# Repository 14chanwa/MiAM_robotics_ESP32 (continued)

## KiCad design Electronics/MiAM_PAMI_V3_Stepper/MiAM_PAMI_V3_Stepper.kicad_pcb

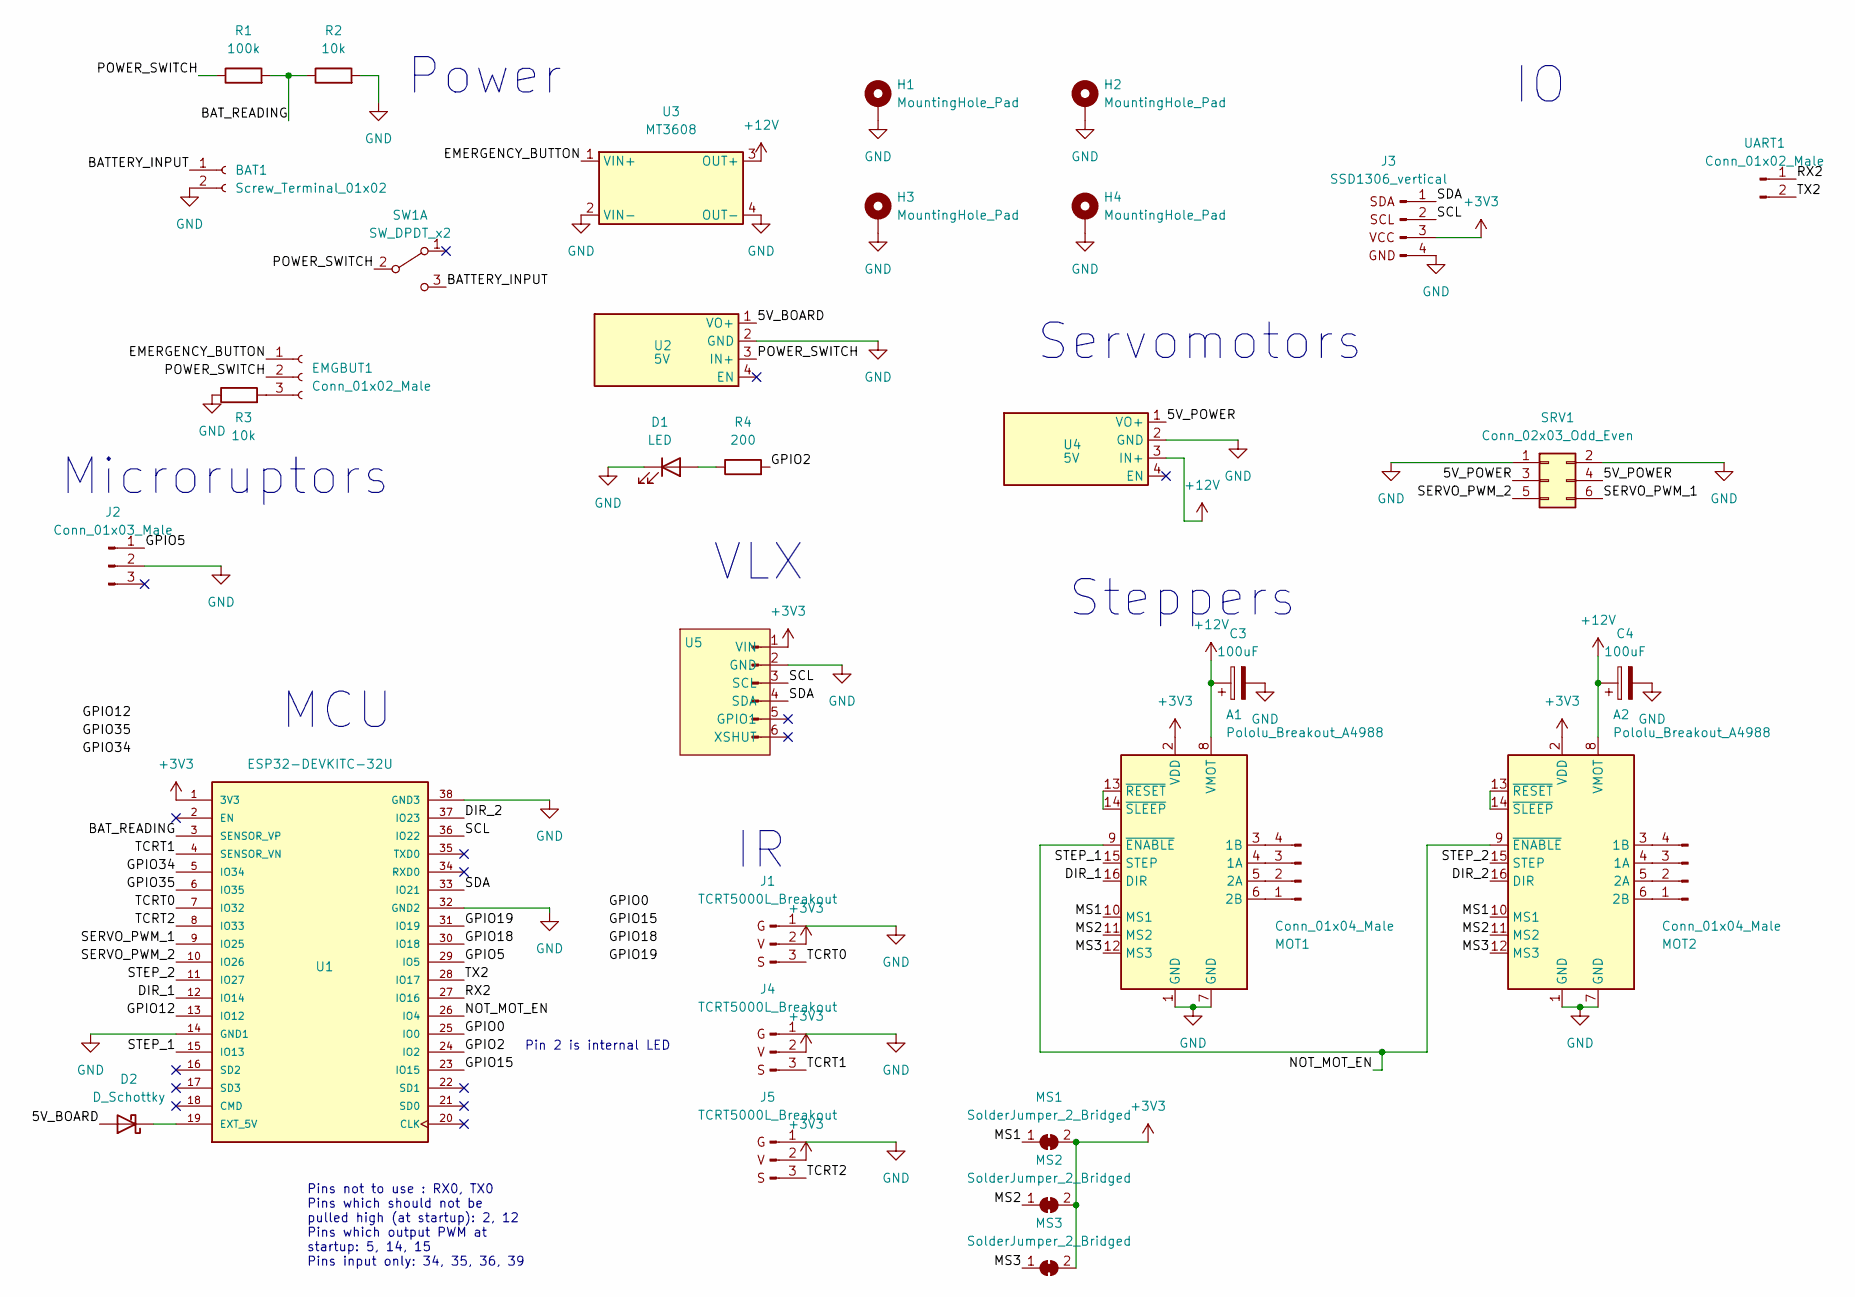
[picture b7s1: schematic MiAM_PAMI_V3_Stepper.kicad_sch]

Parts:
A1, A2: Pololu_Breakout_A4988; Pololu_Breakout-16_15.2x20.3mm
BAT1: Screw_Terminal_01x02; JST_PH_B2B-PH-K_1x02_P2.00mm_Vertical
C3, C4: 100uF; CP_Radial_D6.3mm_P2.50mm
D1: LED; LED_D3.0mm
D2: D_Schottky; D_SOD-323_HandSoldering
EMGBUT1: Conn_01x02_Male; JST_PH_B3B-PH-K_1x03_P2.00mm_Vertical
H1, H2, H3, H4: MountingHole_Pad; MountingHole_3.2mm_M3_DIN965_Pad
J1, J4, J5: TCRT5000L_Breakout
J2: Conn_01x03_Male; Microruptor
J3: SSD1306_vertical
MOT1, MOT2: Conn_01x04_Male; JST_SH_BM04B-SRSS-TB_1x04-1MP_P1.00mm_Vertical
MS1, MS2, MS3: SolderJumper_2_Bridged; SolderJumper-2_P1.3mm_Bridged_RoundedPad1.0x1.5mm
R1: 100k; R_0805_2012Metric_Pad1.20x1.40mm_HandSolder
R2, R3: 10k; R_0805_2012Metric_Pad1.20x1.40mm_HandSolder
R4: 200; R_0805_2012Metric
SRV1: Conn_02x03_Odd_Even; PinHeader_2x03_P2.54mm_Vertical
SW1: SW_DPDT_x2; SS-12D11
U1: ESP32-DEVKITC-32U; ESP32U-ShieldPattern
U2, U4: 5V; VoltageRegulator
U3: MT3608
U5: PinHeader_1x06_P2.54mm_Vertical
UART1: Conn_01x02_Male; PinHeader_1x02_P2.54mm_Vertical

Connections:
+3V3: A1.2 (VDD), A2.2 (VDD), J1.2 (V), J3.3 (VCC), J4.2 (V), J5.2 (V), MS1.2 (B), MS2.2 (B), MS3.2 (B), U1.1 (3V3), U5.1 (VIN)
+12V: A1.8 (VMOT), A2.8 (VMOT), C3.1, C4.1, U3.3 (OUT+), U4.3 (IN+)
/5V_BOARD: D2.2 (A), U2.1 (VO+)
/5V_POWER: SRV1.3, SRV1.4, U4.1 (VO+)
/BATTERY_INPUT: BAT1.1, SW1.3 (C)
/BAT_READING: R1.2, R2.1, U1.3 (SENSOR_VP)
/DIR_1: A1.16 (DIR), U1.12 (IO14)
/DIR_2: A2.16 (DIR), U1.37 (IO23)
/EMERGENCY_BUTTON: EMGBUT1.1, U3.1 (VIN+)
/GPIO0: U1.25 (IO0); also elsewhere on the board
/GPIO2: R4.2, U1.24 (IO2)
/GPIO5: J2.1, U1.29 (IO5)
/GPIO12: U1.13 (IO12); also elsewhere on the board
/GPIO15: U1.23 (IO15); also elsewhere on the board
/GPIO18: U1.30 (IO18); also elsewhere on the board
/GPIO19: U1.31 (IO19); also elsewhere on the board
/GPIO34: U1.5 (IO34); also elsewhere on the board
/GPIO35: U1.6 (IO35); also elsewhere on the board
/MS1: A1.10 (MS1), A2.10 (MS1), MS1.1 (A)
/MS2: A1.11 (MS2), A2.11 (MS2), MS2.1 (A)
/MS3: A1.12 (MS3), A2.12 (MS3), MS3.1 (A)
/NOT_MOT_EN: A1.9 (~ENABLE), A2.9 (~ENABLE), U1.26 (IO4)
/POWER_SWITCH: EMGBUT1.2, R1.1, SW1.2 (B), U2.3 (IN+)
/RX2: U1.27 (IO16), UART1.1
/SCL: J3.2 (SCL), U1.36 (IO22), U5.3 (SCL)
/SDA: J3.1 (SDA), U1.33 (IO21), U5.4 (SDA)
/SERVO_PWM_1: SRV1.6, U1.9 (IO25)
/SERVO_PWM_2: SRV1.5, U1.10 (IO26)
/STEP_1: A1.15 (STEP), U1.15 (IO13)
/STEP_2: A2.15 (STEP), U1.11 (IO27)
/TCRT0: J1.3 (S), U1.7 (IO32)
/TCRT1: J4.3 (S), U1.4 (SENSOR_VN)
/TCRT2: J5.3 (S), U1.8 (IO33)
/TX2: U1.28 (IO17), UART1.2
GND: A1.1 (GND), A1.7 (GND), A2.1 (GND), A2.7 (GND), BAT1.2, C3.2, C4.2, D1.1 (K), H1.1, H2.1, H3.1, H4.1, J1.1 (G), J2.2, J3.4 (GND), J4.1 (G), J5.1 (G), R2.2, R3.1, SRV1.1, SRV1.2, U1.14 (GND1), U1.32 (GND2), U1.38 (GND3), U2.2 (GND), U3.2 (VIN-), U3.4 (OUT-), U4.2 (GND), U5.2 (GND)
unnamed: A1.4 (1A), MOT1.3
unnamed: A1.3 (1B), MOT1.4
unnamed: A1.5 (2A), MOT1.2
unnamed: A1.6 (2B), MOT1.1
unnamed: A1.13 (~RESET), A1.14 (~SLEEP)
unnamed: A2.4 (1A), MOT2.3
unnamed: A2.3 (1B), MOT2.4
unnamed: A2.5 (2A), MOT2.2
unnamed: A2.6 (2B), MOT2.1
unnamed: A2.13 (~RESET), A2.14 (~SLEEP)
unnamed: D1.2 (A), R4.1
unnamed: D2.1 (K), U1.19 (EXT_5V)
unnamed: EMGBUT1.3, R3.2

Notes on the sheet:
Pins not to use : RX0, TX0 Pins which should not be pulled high (at startup): 2, 12 Pins which output PWM at startup: 5, 14, 15 Pins input only: 34, 35, 36, 39
Power
MCU
Microruptors
Pin 2 is internal LED
VLX
Steppers
Servomotors

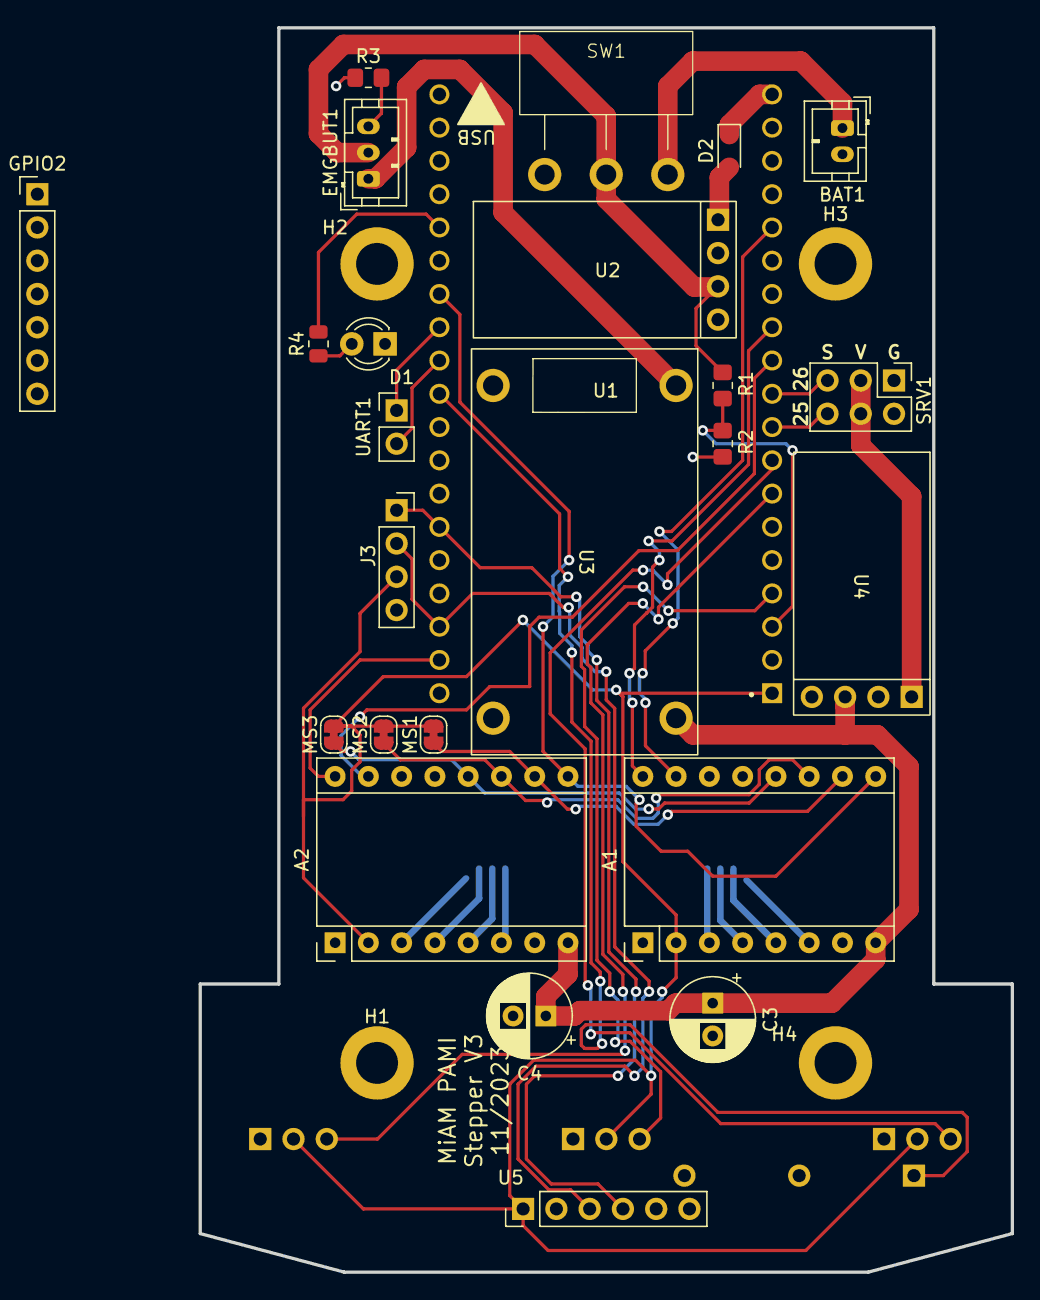
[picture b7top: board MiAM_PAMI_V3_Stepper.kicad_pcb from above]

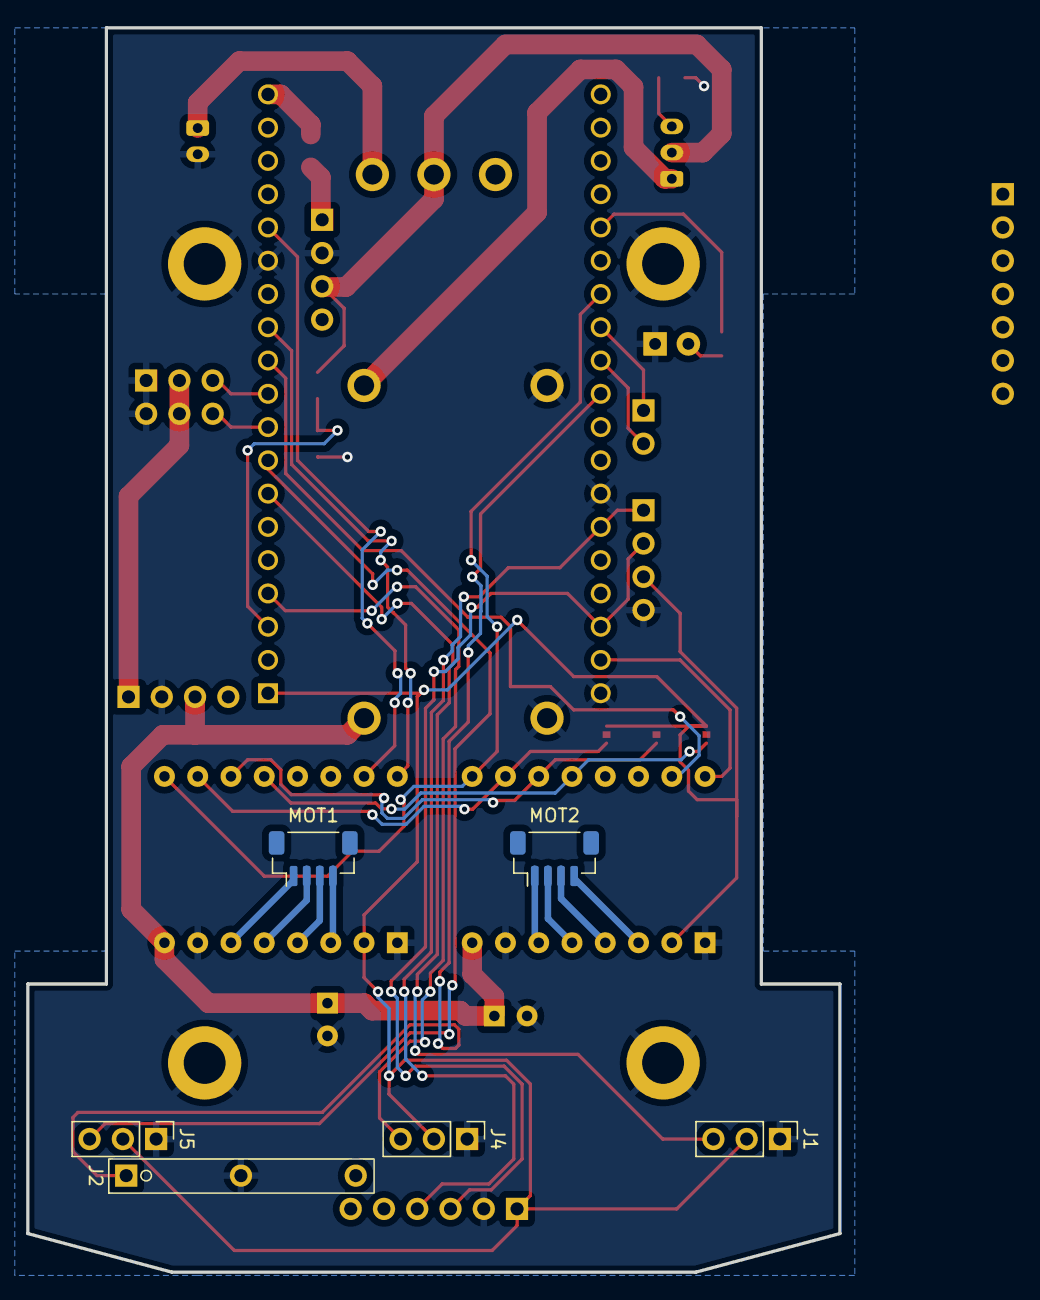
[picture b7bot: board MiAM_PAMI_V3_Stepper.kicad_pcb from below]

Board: 2 copper layers, 62.0 x 95.0 mm, 35 parts (6 on the bottom side), 48 nets.

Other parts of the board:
GPIO2: Conn_01x07_Male; PinHeader_1x07_P2.54mm_Vertical

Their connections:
/GPIO0: GPIO2.1; also elsewhere on the board
/GPIO12: GPIO2.2; also elsewhere on the board
/GPIO15: GPIO2.3; also elsewhere on the board
/GPIO18: GPIO2.4; also elsewhere on the board
/GPIO19: GPIO2.5; also elsewhere on the board
/GPIO34: GPIO2.6; also elsewhere on the board
/GPIO35: GPIO2.7; also elsewhere on the board

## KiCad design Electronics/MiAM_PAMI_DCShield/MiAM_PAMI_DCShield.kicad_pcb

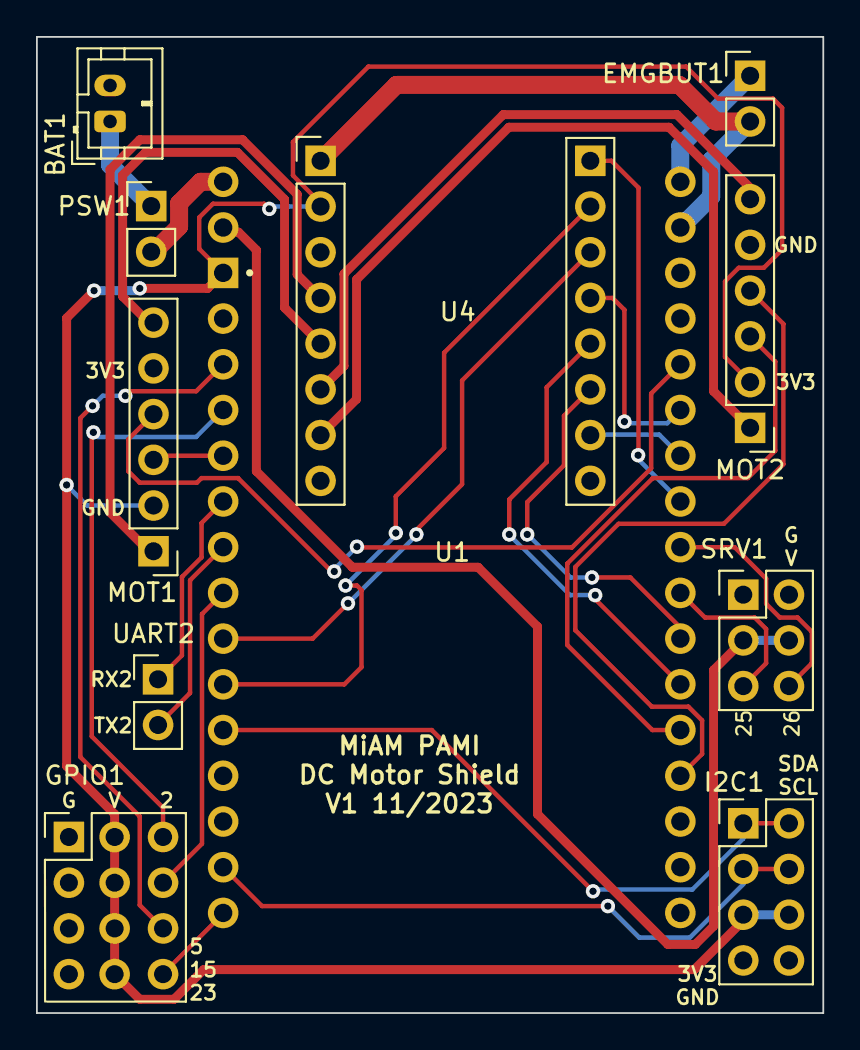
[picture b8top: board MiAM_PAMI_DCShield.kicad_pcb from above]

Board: 2 copper layers, 43.7 x 54.2 mm, 11 parts (0 on the bottom side), 32 nets.

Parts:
BAT1: Screw_Terminal_01x02; JST_PH_B2B-PH-K_1x02_P2.00mm_Vertical
EMGBUT1: Conn_01x02_Male; PinHeader_1x02_P2.54mm_Vertical
GPIO1: PinHeader_3x4_P2.54mm_Vertical
I2C1: Conn_02x04_Odd_Even; PinHeader_2x04_P2.54mm_Vertical
MOT1, MOT2: Conn_01x06_Male; PinHeader_1x06_P2.54mm_Vertical
PSW1: Conn_01x02_Male; PinHeader_1x02_P2.54mm_Vertical
SRV1: Conn_02x03_Odd_Even; PinHeader_2x03_P2.54mm_Vertical
U1: ESP32-DEVKIT-V1; ESP32_ShieldPattern
U4: TB6612FNG
UART2: Conn_01x02_Male; PinHeader_1x02_P2.54mm_Vertical

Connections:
+3V3: GPIO1.5, GPIO1.6, GPIO1.7, GPIO1.8, I2C1.5, I2C1.6, MOT1.2, MOT2.2, U1.1 (3V3), U4.2 (VCC)
+12V: EMGBUT1.1, U1.SH2 (12V)
/1A: U1.9 (D18), U4.14 (AIN1)
/1Y: MOT1.1, U4.4 (AO1)
/2A: U1.10 (D19), U4.15 (AIN2)
/2Y: MOT1.6, U4.5 (AO2)
/3A: U1.21 (D32), U4.12 (BIN1)
/3Y: MOT2.1, U4.7 (BO1)
/4A: U1.22 (D33), U4.11 (BIN2)
/4Y: MOT2.6, U4.6 (BO2)
/5V_POWER: SRV1.3, SRV1.4, U1.SH3 (SERVO_V)
/BATTERY_INPUT: BAT1.1, PSW1.1
/EMERGENCY_BUTTON: EMGBUT1.2, U1.SH1 (EMG_BUT), U4.1 (VM)
/EN12: U1.25 (D27), U4.16 (PWMA)
/EN34: U1.26 (D14), U4.10 (PWMB)
/ENCODER_A1: MOT1.4, U1.28 (D13)
/ENCODER_A2: MOT2.4, U1.19 (D34)
/ENCODER_B1: MOT1.3, U1.5 (D4)
/ENCODER_B2: MOT2.3, U1.20 (D35)
/GPIO2: GPIO1.9, U1.4 (D2)
/GPIO5: GPIO1.10, U1.8 (D5)
/GPIO15: GPIO1.11, U1.3 (D15)
/GPIO23: GPIO1.12, U1.15 (D23)
/POWER_SWITCH: PSW1.2, U1.SH4 (POW_SW)
/RX2: U1.6 (RX2), UART2.1
/SCL: I2C1.3, I2C1.4, U1.14 (D22)
/SDA: I2C1.1, I2C1.2, U1.11 (D21)
/SERVO_PWM_1: SRV1.5, U1.23 (D25)
/SERVO_PWM_2: SRV1.6, U1.24 (D26)
/STBY: U1.27 (D12), U4.13 (STBY)
/TX2: U1.7 (TX2), UART2.2
GND: BAT1.2, GPIO1.1, GPIO1.2, GPIO1.3, GPIO1.4, I2C1.7, I2C1.8, MOT1.5, MOT2.5, SRV1.1, SRV1.2, U1.2 (GND), U1.18 (VN), U1.29 (GND), U4.3 (PGND), U4.8 (PGND), U4.9 (PGND)

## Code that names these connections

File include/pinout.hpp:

#ifndef _PINOUT_HEADER
#define _PINOUT_HEADER

/////////////////////////////////////////////
// Pins
/////////////////////////////////////////////

// #define LED_BUILTIN 2

#define IN1_A 25
#define IN2_A 26
#define IN1_B 32
#define IN2_B 33
#define EN_A 27
#define EN_B 14

#define ENCODER_A1 2
#define ENCODER_B1 4

#define ENCODER_A2 34
#define ENCODER_B2 35

#define BAT_READING 36

/////////////////////////////////////////////
// Resistor values
/////////////////////////////////////////////

#define R1 20000.0
#define R2 4700.0

/////////////////////////////////////////////
// Motor & encoder specs
/////////////////////////////////////////////

#define MOTOR_REDUCTION_FACTOR 100.0
#define MOTOR_RATED_RPM 220.0
#define ENCODER_PULSE_PER_REVOLUTION 28
#define LEFT_ENCODER_ID 0
#define RIGHT_ENCODER_ID 1

#endif

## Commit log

2023-07-31 Start implementing PID
2023-07-31 Write a specific Motor class
2023-07-31 Change unit to rad/s
2023-08-01 Change control unit to PWM
2023-08-05 Put code in a separate folder
2023-08-05 Add first version of pcb
2023-08-06 Add miam utils and kinematics
2023-08-08 Do straight lines & fix params
2023-08-08 Add motioncontroller
2023-08-08 Change calibration trajectory
2023-08-09 Ajoute logger UDP Teleplot
2023-08-09 Use float instead of double to optimize speed
2023-08-09 Add LED heartbeat
2023-08-09 Set compiler optimization
2023-08-09 Fixups
2023-08-09 Add credentials handling
2023-09-02 Update driver and add ota update
2023-10-16 Tweak parameters for new design
2023-10-16 Add first PAMI CAD
2023-10-18 Make more condensed version of pcb
2023-10-23 Make genric robot wheel structure
2023-10-28 Add modular structure for stepper & dc pami
2023-10-28 Fix initial PAMI pcb
2023-10-28 Add 3 PCB for DC & Stepper PAMI
2023-10-28 Fix MT3608 footprint
2023-10-28 Fix shield footprint
2023-11-01 Faster DC
2023-11-03 Add V2 of PAMI stepper
2023-11-03 Fix pcb & add driver board
2023-11-06 Put stepper driver on main board
2023-11-06 Begin optimizing stepper code
2023-11-06 Fix new stepper code
2023-11-06 Switch to ArduinoOTA and cleanup
2023-11-24 Switch to esp-idf+arduino & fix lag issues
2023-11-26 Initial commit PAMI V3
2023-11-26 Init pami v3
2023-11-26 Fix PCB for v3
2023-11-26 Fix pcb v3
2023-11-26 Fixes, adds vlx & tcrt
2023-11-29 PCB order 2023-11-29
2024-01-21 Functional stepper code for a square
2024-01-21 Add ssd1306 and semaphores
2024-02-06 Add DC PAMI board
2024-02-17 Robot now waits for broadcasted traj
2024-02-17 Fix message length bug
2024-02-17 Enhance ssd1306 message
2024-02-18 Add slowdown with vlx
2024-02-18 Fix PCB
2024-02-18 Add message type handling
2024-02-18 Receive IDs
2024-02-18 Fix DC PAMI schematic
2024-02-18 Display ID on screen
2024-02-19 Add match time handling
2024-03-09 Working DC PAMI (need invert one motor)
2024-03-09 Fix invert motor
2024-03-13 Add servo example code
2024-03-13 Clean servo code
2024-03-16 Update code with strategy
2024-03-16 Rework i2c tasks
2024-03-17 Make PAMI listen to UDP broadcasts
2024-03-17 Functional trajectories
2024-03-17 Update positions
2024-03-18 Init git for SupervisorBoard
2024-03-22 Make ethernet listening
2024-03-22 Add SupervisorBoard tft screen & routing
2024-03-25 Complete supervisor PCB
2024-03-25 Add front switches code
2024-03-29 Rework code structure
2024-03-30 Add telemetry handler & bf blinking
2024-03-30 Add Message parsing
2024-03-30 Fix TCP issue (not closing connections)
2024-03-30 Add PAMI message
2024-03-31 Fix issue with newer C++ versions
2024-03-31 Finish MatchState machine for robot loop & multiple BFs
2024-03-31 BF telemetry DC
2024-04-05 Block steppers in match ended state, handle switches, send reports to scd
2024-04-05 Add miam utils to SupervisorBoard, start interface
2024-04-05 Put report broadast in message handling
2024-04-06 Fix message sending & receiving for PAMI
2024-04-06 Add missing lib
2024-04-06 Add match
2024-04-06 Use wifi for SCD
2024-04-07 Return message
2024-04-07 Fix segfault in message sender
2024-04-07 BF comms: pami requests respnse
2024-04-28 Use float arrays as buffers for message
2024-04-28 Add tirette functionnality
2024-05-04 Add comm delay and battery voltage info
2024-05-04 Add lock motors option
2024-05-04 Add Supervisor Servo
2024-05-04 BF waiting time PAMI
2024-05-04 BF yellow side inversion
2024-05-05 Add exclusion zone at the end and bf
2024-05-05 Add branching for pami 5 based on vlx
2024-05-06 Add alternative routes PAMI
2024-05-06 Fix traj continuation and begin avoidance
2024-05-06 Add avoidance for PAMI
2024-05-07 Enhance avoidance
2024-05-07 Catchup trajectory is now continuous
2024-05-07 Avoidance trajectories are now velocity-continuous
2024-05-07 BF pami & set supervisor board match code
2024-05-07 Put avoidance in an other file
2024-05-07 Code tuesday evening
2024-05-07 Remove clear trajectories from old avoidance and add conditions on obstacle position
2024-05-09 Add VLX code for Stonks Robotics
2024-05-10 Add PAMI for Stonks Industries
2024-07-23 Switch to touchscreen
2024-07-24 Make clickable touch buttons
2024-07-26 Implement clickable button and switch to asynctcp
2024-08-18 Apparently fix issues with asynctcp lib
2024-08-18 Fix tasks priorities
2024-08-18 Clean supervisor board project
2024-08-18 Add miam_utils_arduino to CommonLibraries
2024-08-18 Add message to CommonLibraries
2024-08-18 Add adc_reading and teleplot_arduino to CommonLibraries
2024-08-18 Add button to CommonLibraries
2024-08-25 Reorganise projects
2024-08-25 Add 2024 avoidance robot
2024-08-25 Init 2024 supervisor board
2024-08-26 Put Bluetooth code on a separate card connected with serial
2024-08-26 Revamp anti-bounce button library
2024-08-26 Async connect wifi & update logs
2024-08-26 Implement stepper control
2024-08-26 Set secret.hpp as ln
2024-10-13 Begin 2025 PAMI
2024-11-11 Add new PAMI PCB
2024-11-18 Add LED ring and better routing
2024-12-01 Fix PAMI pcb
2024-12-01 Add additional breakout for BW16
2025-01-02 Update PCB
2025-01-02 Add 2025 robot code
2025-01-03 Add communication using BW16
2025-01-03 Rework Message api
2025-01-05 Handle 3 vlx
2025-02-22 Update PAMI code: leds and fix pid
2025-02-22 BF message parsing template
2025-02-22 Add LED ring to PAMI
2025-02-23 Switch lcd library to TFT_eSPI
2025-02-23 Rework tft drawables into lib
2025-02-23 Init presentation board code
2025-03-15 Functional PAMI test code starting at 85
2025-03-24 Work from last session
2025-04-19 Add bottom vlx for superstar pami
2025-04-20 AvoidanceRobot: Use ESP32 remote instead of bt
2025-04-20 Fix avoidance robot movement
2025-05-08 Update PAMI strat
2025-05-09 Add PAMI Tank and Remote & fix robotbasedc
2025-05-09 Make strategies for pamis
2025-05-10 Make trajectories for pami 2 & 4
2025-05-10 Fix avoidance robot code for new remote orientation
2025-05-11 Fix issue with deadzone pamitank
2025-05-11 Update tft presentation board
2025-05-11 Fix pami traj
2025-05-25 Fix switch logic & add specific behavior at match start
2025-05-25 Add blink mode for presentation board
2025-05-26 Fix PAMI trajs v1
2025-05-26 New PAMI trajs
2025-05-26 Add leds for avoidance robot
2025-05-26 Fix sup board 100s & implement integration in AvoidanceRobot
2025-07-05 Last modifs for match codes in 2025
2025-07-05 Rename folders according to yearing conventions
2025-07-06 Init eurobot2026 with mqtt
2025-07-06 Add robot position to pami state message
2026-02-07 Revert mqtt changes for eurobot 2026
2026-03-29 Make trajectories for 2026
2026-03-29 Add robot in end zone
2026-03-29 Revert slave board to old code
2026-04-25 Init VLXReader files
2026-04-25 Create classes for vlx reader
2026-04-25 Improve VLX reader
2026-04-25 Add leds on vlx reader
2026-04-25 Fix colors
2026-04-26 Add global proximity led
2026-05-10 Init squirel code
2026-05-10 Update supervisor board code for squirel
2026-05-10 Implement sts base
2026-05-11 Make squirel communicate using wifi
2026-05-11 BF systeme calcul deporte pami 6
2026-05-11 Working pump code
2026-05-11 First strat
2026-05-11 Implement serial com with rpi
2026-05-12 Strat debut mardi
2026-05-12 Functional code for squirel
2026-05-12 Kind of working squirel avoidance
2026-05-12 Hard type int32 in serial com for vlxreader
2026-05-12 New pami code with new arm
2026-05-13 STSServo: use position increment instead of speed.
2026-05-13 Add funny action
2026-05-13 Hardcode strategy in steps
2026-05-14 Second match code
2026-05-14 3rd match code & fix false positive avoidance
2026-05-14 New vlx code with angle
2026-05-14 Fix aperture vlx
2026-05-15 Fix Squirel code & 4th match code
2026-05-15 Add esp32 s3 zero symbol
2026-05-16 5th match code go forward 20mm
2026-05-16 Working code with push crates
2026-05-16 Final strategy for squirel go back to push
2026-05-17 Finals match code
